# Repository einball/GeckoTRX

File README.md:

# GeckoTRX
GeckoTRX Assembly Design Files

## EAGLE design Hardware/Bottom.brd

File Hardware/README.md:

# GeckoTRX Hardware Design Files

GeckoTRX Hardware Repository

## Getting Started

GeckoTRX is a palm-sized Software Defined Radio with a focus on my own education and be a fun project in my spare time. The repository you are looking at is hosting the front assembly of the project, both hardware design files and software source files required to build the project. If you haven't done any programming or software development yet, or just want to download the latest release of the firmware, you may want to have a look at the [Quickstart Guide](#).

## Prerequisites

In order to view the hardware design files, you will need to obtain a copy of [Autodesk's EagleCAD](https://www.autodesk.com/products/eagle/) which is freely available to view the hardware design files. 

The front assembly uses a EFM8BB1 microcontroller which features a 8051 core alongside with the neccessary peripherals to drive the LED's to indicate the transceivers status.

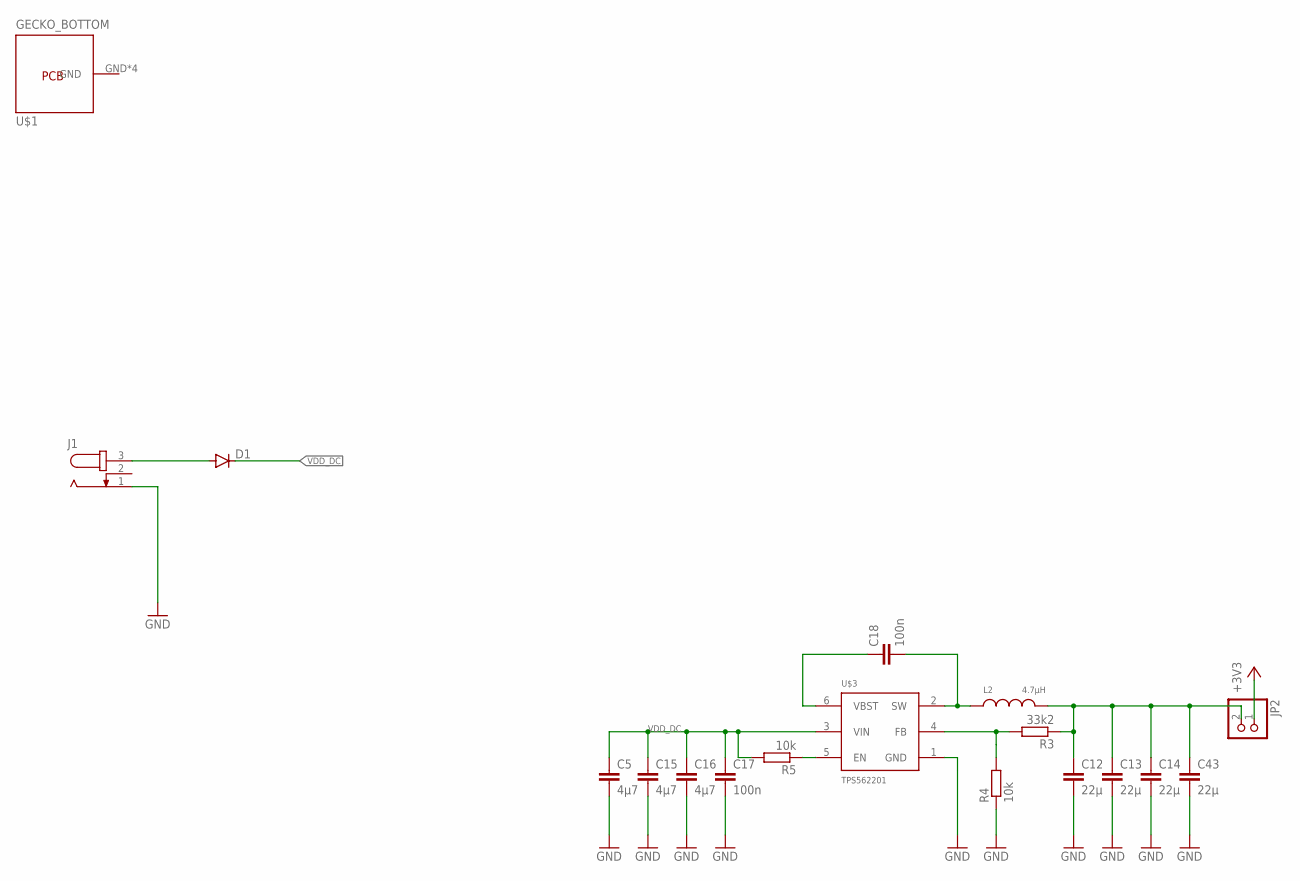
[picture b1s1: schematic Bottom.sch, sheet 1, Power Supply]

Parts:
C5, C15, C16: 4µ7; C0805
C12, C13, C14, C43: 22µ; C0805
C17, C18: 100n; C0805
D1: DIODE-SMB; SMB
J1: JACK-PLUG0; SPC4077
JP2: PINHD-1X2; 1X02
L2: 4.7µH; WE-MAPI_3015/3020
R3: 33k2; R0805
R4, R5: 10k; R0805
U$1: GECKO_BOTTOM
U$3: TPS562201; SOT95P280X110-6

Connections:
+3V3: JP2.1; also elsewhere on the board
GND: C5.2, C12.2, C13.2, C14.2, C15.2, C16.2, C17.2, C43.2, J1.1, R4.1, U$3.1 (GND); also elsewhere on the board
unnamed: D1.A, J1.3
unnamed: C18.1, U$3.6 (VBST)
unnamed: C18.2, L2.1, U$3.2 (SW)
unnamed: R3.2, R4.2, U$3.4 (FB)
unnamed: C12.1, C13.1, C14.1, C43.1, JP2.2, L2.2, R3.1
VDD_DC: C5.1, C15.1, C16.1, C17.1, D1.C, R5.2, U$3.3 (VIN)
VREG_VDD3V3_EN: R5.1, U$3.5 (EN)

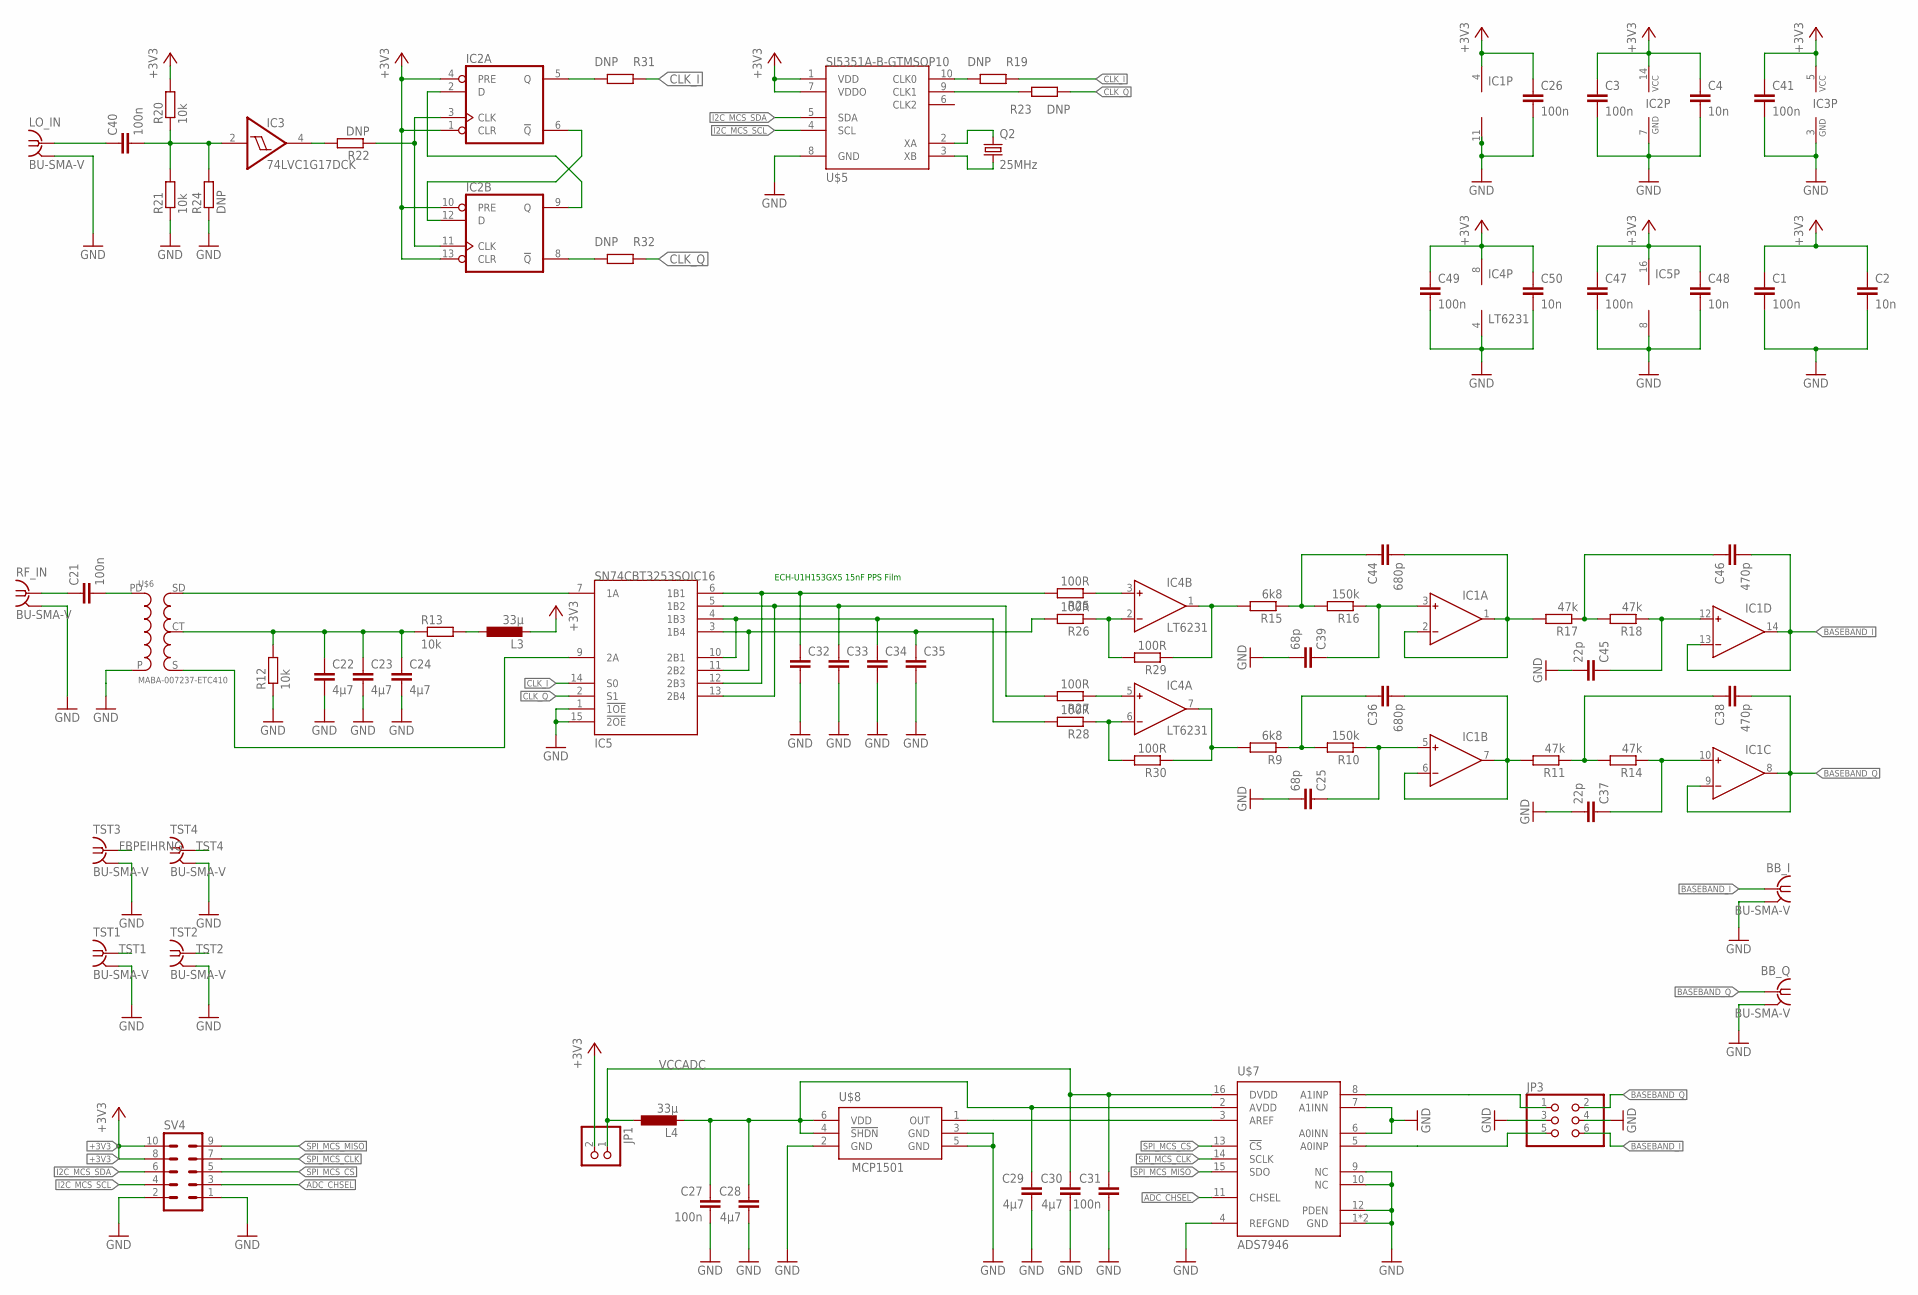
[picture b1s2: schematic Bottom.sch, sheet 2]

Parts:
BB_I: BU-SMA-V
BB_Q: BU-SMA-V
C1, C3, C21, C26, C27, C31, C40, C41, C47, C49: 100n; C0603
C2, C4, C48, C50: 10n; C0603
C22, C23, C24, C28, C29, C30: 4µ7; C0805
C25, C39: 68p; C0603
C32, C33, C34, C35: C-EUC1206; C1206
C36, C44: 680p; C0603
C37, C45: 22p; C0603
C38, C46: 470p; C0603
IC1: OP491SOIC_N14; SOIC127P600X155-14
IC2: 74AC74D; SO14
IC3: 74LVC1G17DCK; SC70-5
IC4: LT6231; SO8
IC5: SN74CBT3253SOIC16; SOIC127P600X175-16
JP1: PINHD-1X2; 1X02
JP3: PINHD-2X3; 2X03
L3, L4: 33µ; L2012C
LO_IN: BU-SMA-V
Q2: 25MHz; ABM10W
R9, R15: 6k8; R0603
R10, R16: 150k; R0603
R11, R14, R17, R18: 47k; R0603
R12, R13, R20, R21: 10k; R0603
R19, R22, R23, R24, R31, R32: DNP; R0603
R25, R26, R27, R28, R29, R30: 100R; R0603
RF_IN: BU-SMA-V
SV4: MA05-2
TST1, TST2, TST3, TST4: BU-SMA-V
U$5: SI5351A-B-GTMSOP10; SOP50P490X110-10
U$6: MABA-007237-ETC410
U$7: ADS7946; QFN50P300X300X80-17T170
U$8: MCP1501; SOT95P280X110-6

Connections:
+3V3: C1.1, C2.1, C3.1, C4.1, C26.1, C41.1, C47.1, C48.1, C49.1, C50.1, IC1.4 (V+), IC2.1 (CLR), IC2.4 (PRE), IC2.10 (PRE), IC2.13 (CLR), IC2.14 (VCC), IC3.5 (VCC), IC4.8 (V+), IC5.16 (V+), JP1.2, L3.2, R20.2, SV4.8, SV4.10, U$5.1 (VDD), U$5.7 (VDDO); also elsewhere on the board
ADC_CHSEL: SV4.3, U$7.11 (CHSEL)
BASEBAND_I: BB_I.1, C46.2, IC1.13 (IN-), IC1.14 (OUT), JP3.6
BASEBAND_Q: BB_Q.1, C38.2, IC1.8 (OUT), IC1.9 (IN-), JP3.2
CLK_I: IC5.14 (S0), R19.1, R31.1
CLK_Q: IC5.2 (S1), R23.1, R32.1
FBPEIHRNG: TST3.1
GND: BB_I.2, BB_I.3 (2), BB_I.4 (2), BB_I.5 (2), BB_Q.2, BB_Q.3 (2), BB_Q.4 (2), BB_Q.5 (2), C1.2, C2.2, C3.2, C4.2, C22.2, C23.2, C24.2, C25.2, C26.2, C27.2, C28.2, C29.2, C30.2, C31.2, C32.2, C33.2, C34.2, C35.2, C37.2, C39.2, C41.2, C45.2, C47.2, C48.2, C49.2, C50.2, IC1.11 (V-), IC2.7 (GND), IC3.3 (GND), IC4.4 (V-), IC5.1 (!1OE), IC5.8 (V-), IC5.15 (!2OE), JP3.3, JP3.4, LO_IN.2, LO_IN.3 (2), LO_IN.4 (2), LO_IN.5 (2), R12.1, R21.1, R24.1, RF_IN.2, RF_IN.3 (2), RF_IN.4 (2), RF_IN.5 (2), SV4.1, SV4.2, TST1.2, TST1.3 (2), TST1.4 (2), TST1.5 (2), TST2.2, TST2.3 (2), TST2.4 (2), TST2.5 (2), TST3.2, TST3.3 (2), TST3.4 (2), TST3.5 (2), TST4.2, TST4.3 (2), TST4.4 (2), TST4.5 (2), U$5.8 (GND), U$6.P, U$7.1 (GND), U$7.4 (REFGND), U$7.6 (A0INN), U$7.7 (A1INN), U$7.9 (NC), U$7.10 (NC), U$7.12 (PDEN), U$7.17 (GND), U$8.2 (GND), U$8.3 (GND), U$8.5 (GND); also elsewhere on the board
I2C_MCS_SCL: SV4.4, U$5.4 (SCL)
I2C_MCS_SDA: SV4.6, U$5.5 (SDA)
unnamed: R19.2, U$5.10 (CLK0)
unnamed: IC2.3 (CLK), IC2.11 (CLK), R22.1
unnamed: IC2.6 (!Q), IC2.12 (D)
unnamed: IC2.2 (D), IC2.9 (Q)
unnamed: R23.2, U$5.9 (CLK1)
unnamed: IC4.7 (OUT), R9.2, R30.1
unnamed: C36.1, R9.1, R10.2
unnamed: C25.1, IC1.5 (IN+), R10.1
unnamed: C36.2, IC1.6 (IN-), IC1.7 (OUT), R11.2
unnamed: C21.1, RF_IN.1
unnamed: C21.2, U$6.PD
unnamed: C22.1, C23.1, C24.1, R12.2, R13.1, U$6.CT
unnamed: L3.1, R13.2
unnamed: IC4.3 (IN+), R25.1
unnamed: C32.1, IC5.6 (1B1), IC5.12 (2B3), R25.2
unnamed: JP3.1, U$7.8 (A1INP)
unnamed: U$7.3 (AREF), U$8.1 (OUT)
unnamed: C27.1, C28.1, C29.1, L4.2, U$7.2 (AVDD), U$8.4 (!SHDN), U$8.6 (VDD)
unnamed: JP3.5, U$7.5 (A0INP)
unnamed: C38.1, R11.1, R14.2
unnamed: C34.1, IC5.4 (1B3), IC5.10 (2B1), R28.2
unnamed: C37.1, IC1.10 (IN+), R14.1
unnamed: IC4.2 (IN-), R26.1, R29.2
unnamed: Q2.1, U$5.3 (XB)
unnamed: C44.1, R15.1, R16.2
unnamed: C39.1, IC1.3 (IN+), R16.1
unnamed: C44.2, IC1.1 (OUT), IC1.2 (IN-), R17.2
unnamed: IC4.5 (IN+), R27.1
unnamed: C40.1, LO_IN.1
unnamed: C40.2, IC3.2 (I), R20.1, R21.2, R24.2
unnamed: IC3.4 (O), R22.2
unnamed: C46.1, R17.1, R18.2
unnamed: IC5.9 (2A), U$6.S
unnamed: IC5.7 (1A), U$6.SD
unnamed: C45.1, IC1.12 (IN+), R18.1
unnamed: IC4.6 (IN-), R28.1, R30.2
unnamed: Q2.3 (2), U$5.2 (XA)
unnamed: IC4.1 (OUT), R15.2, R29.1
unnamed: IC2.8 (!Q), R32.2
unnamed: IC2.5 (Q), R31.2
unnamed: C35.1, IC5.3 (1B4), IC5.11 (2B2), R26.2
unnamed: C33.1, IC5.5 (1B2), IC5.13 (2B4), R27.2
SPI_MCS_CLK: SV4.7, U$7.14 (SCLK)
SPI_MCS_CS: SV4.5, U$7.13 (!CS)
SPI_MCS_MISO: SV4.9, U$7.15 (SDO)
TST1: TST1.1
TST2: TST2.1
TST4: TST4.1
VCCADC: C30.1, C31.1, JP1.1, L4.1, U$7.16 (DVDD)

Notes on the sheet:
ECH-U1H153GX5 15nF PPS Film

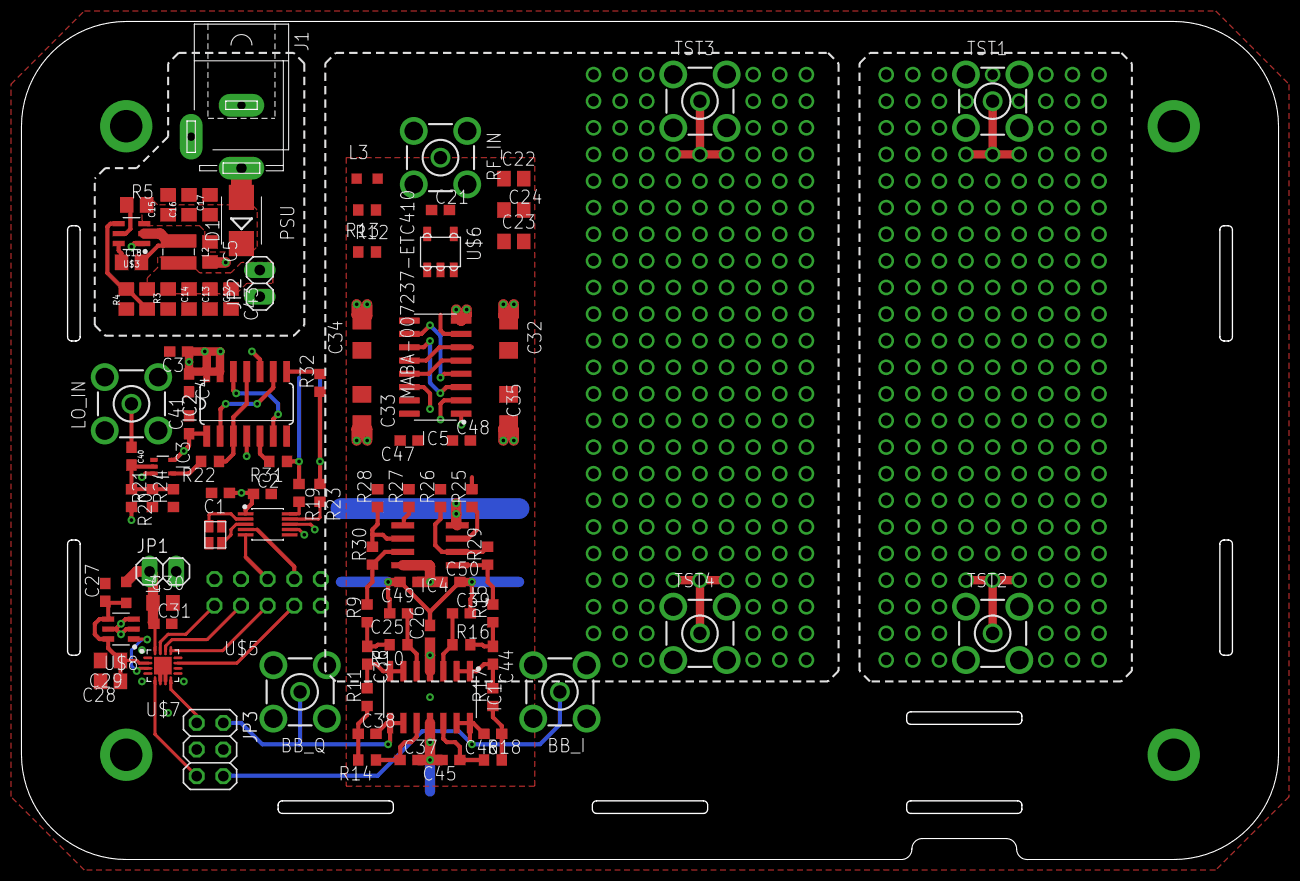
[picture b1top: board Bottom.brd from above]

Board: 4 copper layers, 120.0 x 80.0 mm, 97 parts (1 on the bottom side), 62 nets.

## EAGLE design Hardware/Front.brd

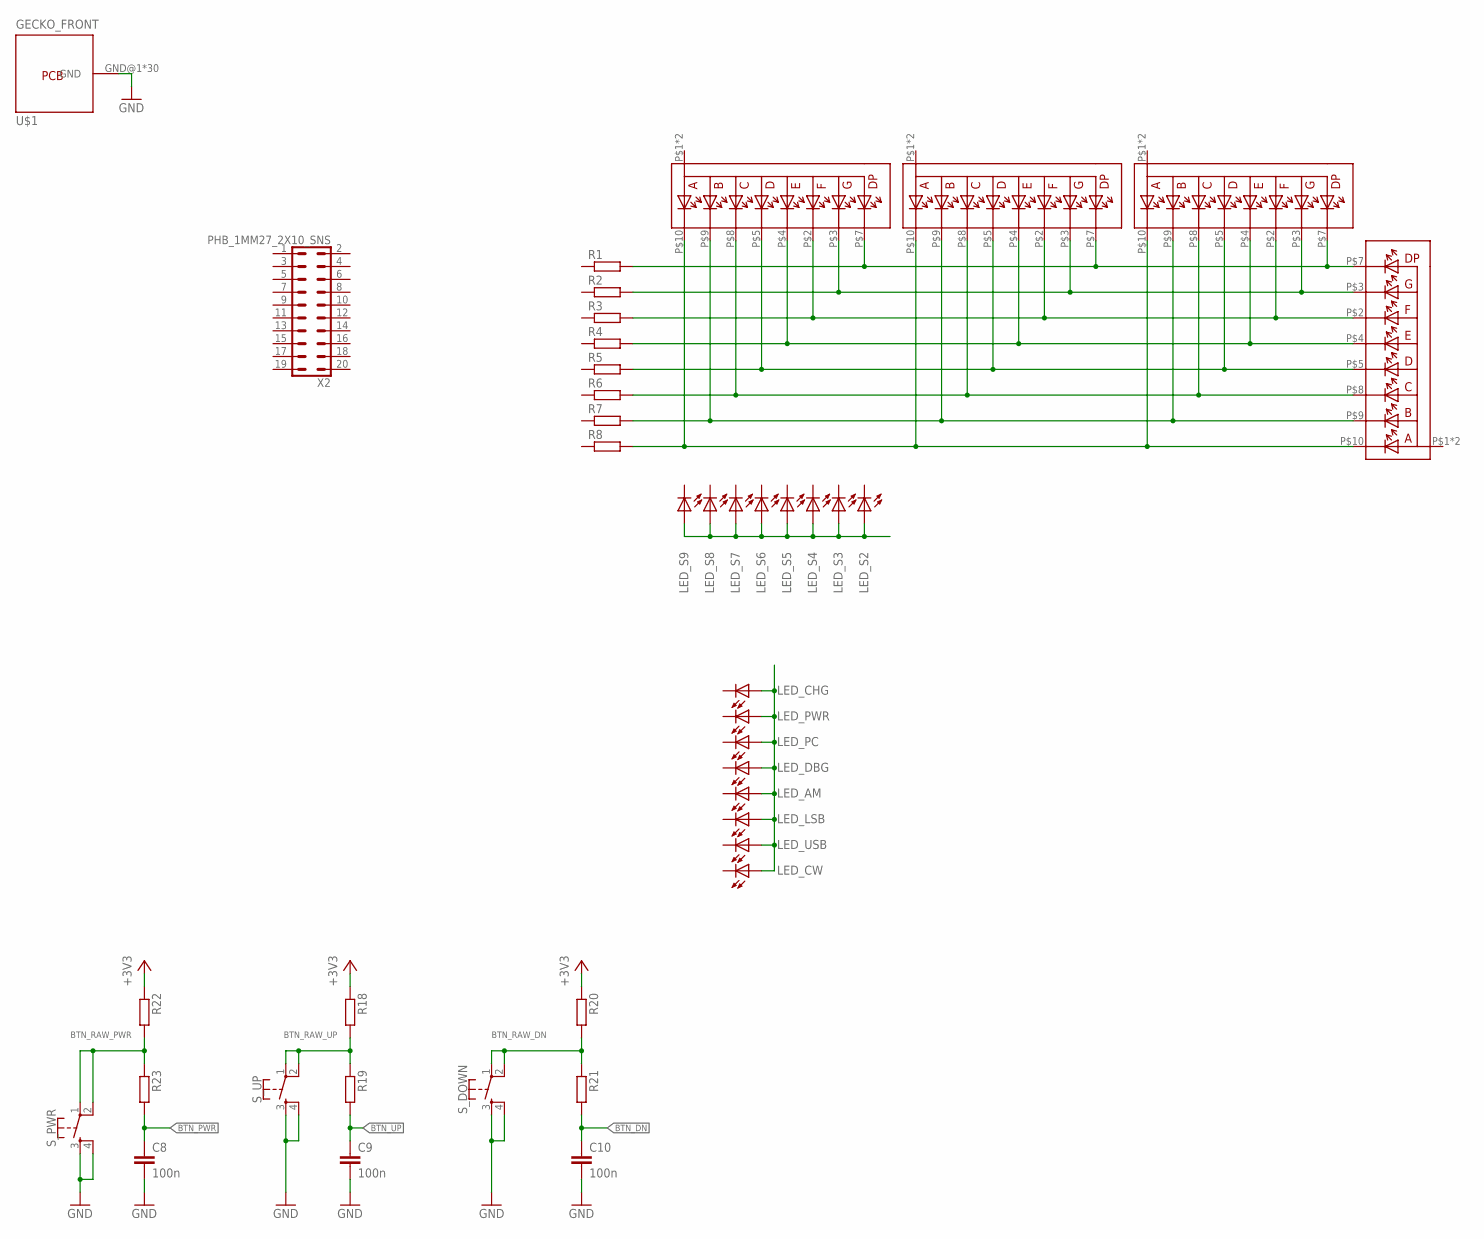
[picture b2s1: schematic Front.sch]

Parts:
C8, C9, C10: 100n; C0402
D3: HDSP-C3E1; 7SEG_THT
LED_AM: LEDCHIPLED_0603; CHIPLED_0603; MPN SML-E12UWT86
LED_CHG: LEDCHIPLED_0603; CHIPLED_0603; MPN SML-E12UWT86
LED_CW: LEDCHIPLED_0603; CHIPLED_0603; MPN SML-E12UWT86
LED_DBG: LEDCHIPLED_0603; CHIPLED_0603; MPN SML-E12UWT86
LED_LSB: LEDCHIPLED_0603; CHIPLED_0603; MPN SML-E12UWT86
LED_PC: LEDCHIPLED_0603; CHIPLED_0603; MPN SML-E12UWT86
LED_PWR: LEDCHIPLED_0603; CHIPLED_0603; MPN SML-E12UWT86
LED_S2, LED_S3, LED_S4, LED_S5, LED_S6, LED_S7, LED_S8, LED_S9: LEDCHIPLED_0603; CHIPLED_0603; MPN SML-E12UWT86
LED_USB: LEDCHIPLED_0603; CHIPLED_0603; MPN SML-E12UWT86
R1, R2, R3, R4, R5, R6, R7, R8, R18, R19, R20, R21, R22, R23: R-EU_R0402; R0402
S_DOWN: MOMENTARY-SWITCH-SPST-2-SMD-4.6X2.8MM; TACTILE_SWITCH_SMD_4.6X2.8MM
S_PWR: MOMENTARY-SWITCH-SPST-2-SMD-4.6X2.8MM; TACTILE_SWITCH_SMD_4.6X2.8MM
S_UP: MOMENTARY-SWITCH-SPST-2-SMD-4.6X2.8MM; TACTILE_SWITCH_SMD_4.6X2.8MM
U$1: GECKO_FRONT
U$9, U$10, U$11: HDSP-C3E1; 7SEG_THT
X2: PHB_1MM27_2X10_SNS

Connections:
+3V3: R18.1, R20.1, R22.1
BTN_DN: C10.1, R21.2
BTN_PWR: C8.1, R23.2
BTN_RAW_DN: R20.2, R21.1, S_DOWN.1, S_DOWN.2
BTN_RAW_PWR: R22.2, R23.1, S_PWR.1, S_PWR.2
BTN_RAW_UP: R18.2, R19.1, S_UP.1, S_UP.2
BTN_UP: C9.1, R19.2
GND: C8.2, C9.2, C10.2, S_DOWN.3, S_DOWN.4, S_PWR.3, S_PWR.4, S_UP.3, S_UP.4, U$1.GND@1, U$1.GND@2, U$1.GND@3, U$1.GND@4, U$1.GND@5, U$1.GND@6, U$1.GND@7, U$1.GND@8, U$1.GND@9, U$1.GND@10, U$1.GND@11, U$1.GND@12, U$1.GND@13, U$1.GND@14, U$1.GND@15, U$1.GND@16, U$1.GND@17, U$1.GND@18, U$1.GND@19, U$1.GND@20, U$1.GND@21, U$1.GND@22, U$1.GND@23, U$1.GND@24, U$1.GND@25, U$1.GND@26, U$1.GND@27, U$1.GND@28, U$1.GND@29, U$1.GND@30
unnamed: D3.P$7 (DP), R1.2, U$9.P$7 (DP), U$10.P$7 (DP), U$11.P$7 (DP)
unnamed: D3.P$3 (G), R2.2, U$9.P$3 (G), U$10.P$3 (G), U$11.P$3 (G)
unnamed: D3.P$2 (F), R3.2, U$9.P$2 (F), U$10.P$2 (F), U$11.P$2 (F)
unnamed: D3.P$4 (E), R4.2, U$9.P$4 (E), U$10.P$4 (E), U$11.P$4 (E)
unnamed: D3.P$5 (D), R5.2, U$9.P$5 (D), U$10.P$5 (D), U$11.P$5 (D)
unnamed: D3.P$8 (C), R6.2, U$9.P$8 (C), U$10.P$8 (C), U$11.P$8 (C)
unnamed: D3.P$9 (B), R7.2, U$9.P$9 (B), U$10.P$9 (B), U$11.P$9 (B)
unnamed: D3.P$10 (A), R8.2, U$9.P$10 (A), U$10.P$10 (A), U$11.P$10 (A)
unnamed: LED_AM.A, LED_CHG.A, LED_CW.A, LED_DBG.A, LED_LSB.A, LED_PC.A, LED_PWR.A, LED_USB.A
unnamed: LED_S2.A, LED_S3.A, LED_S4.A, LED_S5.A, LED_S6.A, LED_S7.A, LED_S8.A, LED_S9.A

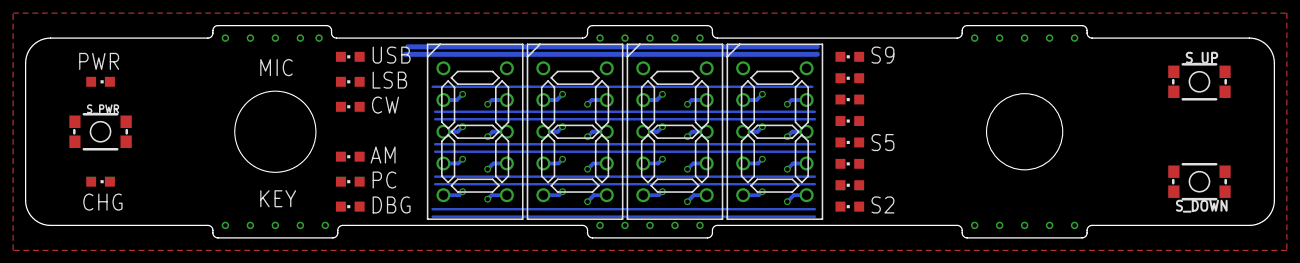
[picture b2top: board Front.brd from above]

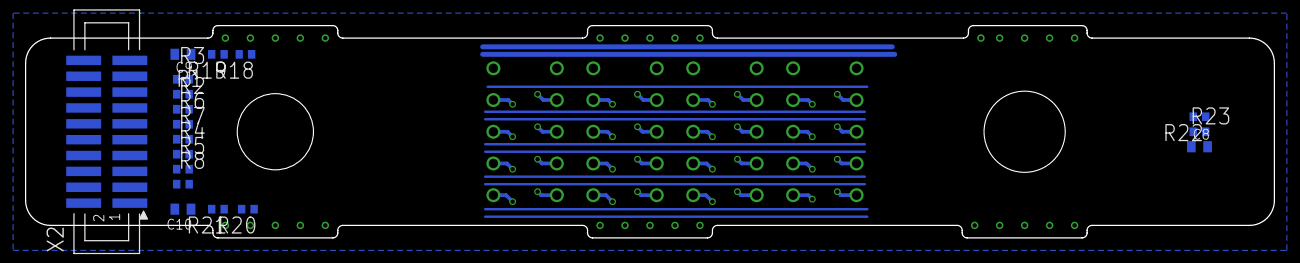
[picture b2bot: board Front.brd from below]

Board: 2 copper layers, 100.0 x 17.0 mm, 42 parts (18 on the bottom side), 18 nets.

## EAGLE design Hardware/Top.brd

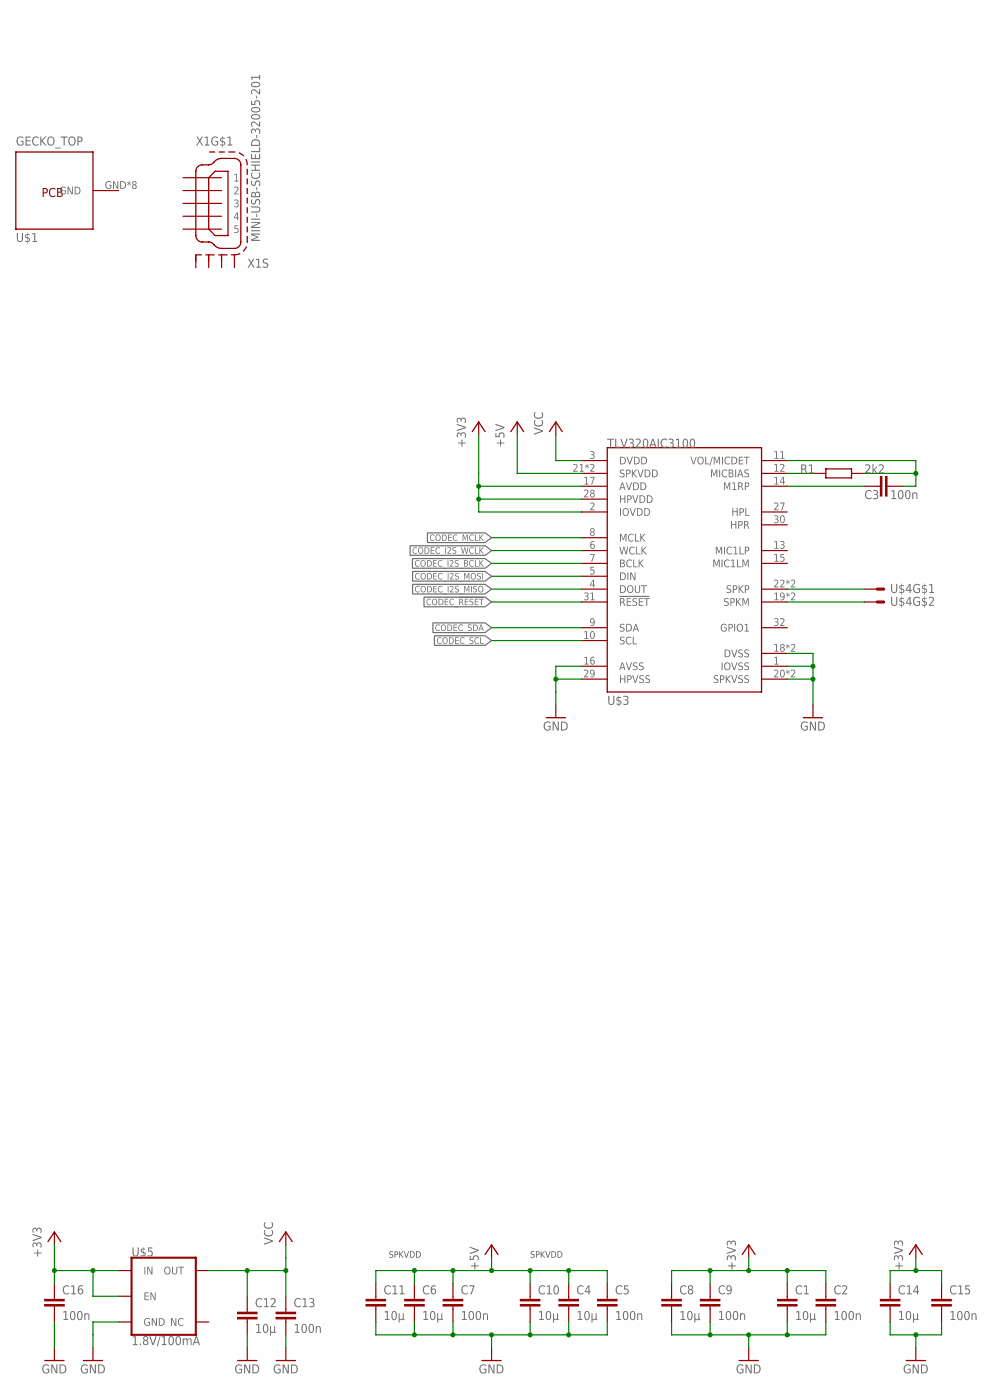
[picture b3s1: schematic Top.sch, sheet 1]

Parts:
C1, C4, C6, C8, C10, C11, C12, C14: 10µ; C0805
C2, C3, C5, C7, C9, C13, C15, C16: 100n; C0805
R1: 2k2; R0402
U$1: GECKO_TOP
U$3: TLV320AIC3100; QFN32
U$4: JST-SH-2-SMT
U$5: 1.8V/100mA; SC70
X1: MINI-USB-SCHIELD-32005-201; 32005-201

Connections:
+3V3: C1.1, C2.1, C8.1, C9.1, C14.1, C15.1, C16.1, U$3.2 (IOVDD), U$3.17 (AVDD), U$3.28 (HPVDD), U$5.1 (IN), U$5.3 (EN)
+5V: C4.1, C5.1, C6.1, C7.1, C10.1, C11.1, U$3.21 (SPKVDD), U$3.24 (SPKVDD)
CODEC_!RESET: U$3.31 (!RESET)
CODEC_I2S_BCLK: U$3.7 (BCLK); also elsewhere on the board
CODEC_I2S_MISO: U$3.4 (DOUT); also elsewhere on the board
CODEC_I2S_MOSI: U$3.5 (DIN); also elsewhere on the board
CODEC_I2S_WCLK: U$3.6 (WCLK); also elsewhere on the board
CODEC_MCLK: U$3.8 (MCLK); also elsewhere on the board
CODEC_SCL: U$3.10 (SCL)
CODEC_SDA: U$3.9 (SDA)
GND: C1.2, C2.2, C4.2, C5.2, C6.2, C7.2, C8.2, C9.2, C10.2, C11.2, C12.2, C13.2, C14.2, C15.2, C16.2, U$3.1 (IOVSS), U$3.16 (AVSS), U$3.18 (DVSS), U$3.20 (SPKVSS), U$3.25 (SPKVSS), U$3.29 (HPVSS), U$3.EXP (DVSS), U$5.2 (GND); also elsewhere on the board
unnamed: U$3.22 (SPKP), U$3.26 (SPKP), U$4.1
unnamed: R1.1, U$3.12 (MICBIAS)
unnamed: C3.1, U$3.14 (M1RP)
unnamed: C3.2, R1.2, U$3.11 (VOL/MICDET)
unnamed: U$3.19 (SPKM), U$3.23 (SPKM), U$4.2
VCC: C12.1, C13.1, U$3.3 (DVDD), U$5.5 (OUT); also elsewhere on the board

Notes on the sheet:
SPKVDD

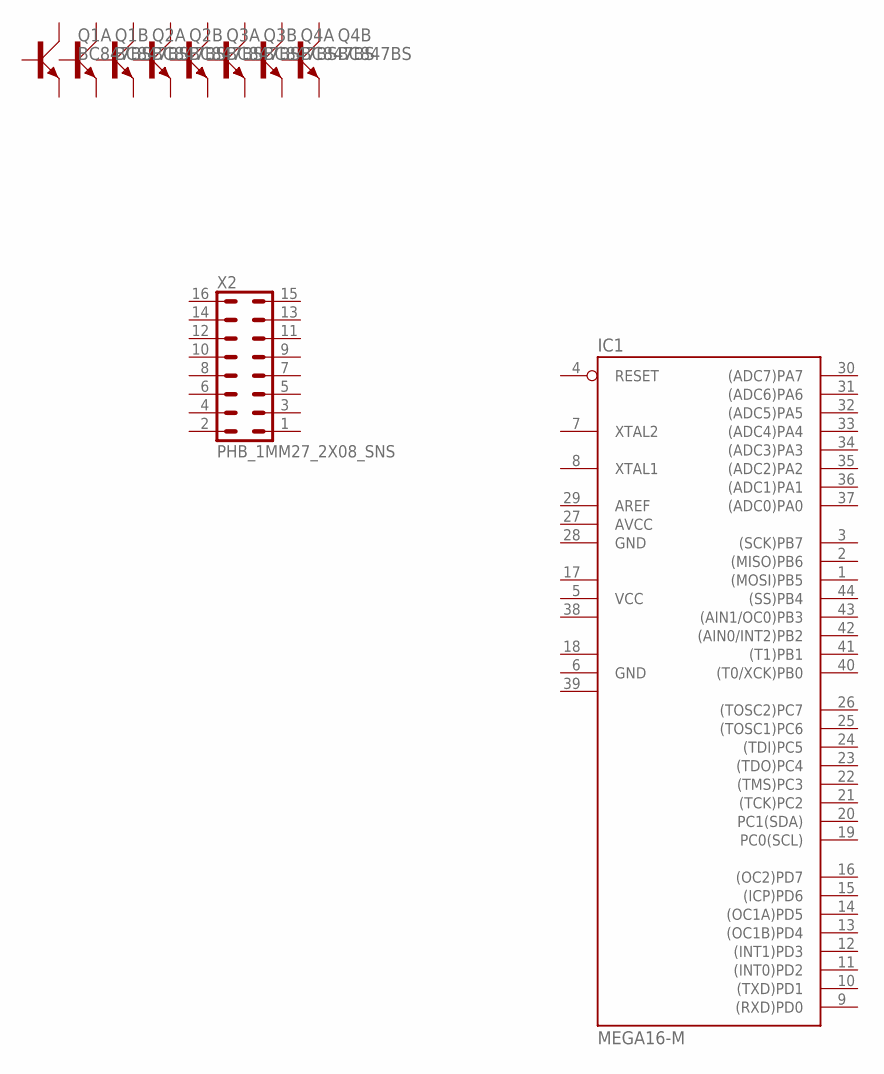
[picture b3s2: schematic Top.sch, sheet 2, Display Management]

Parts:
IC1: MEGA16-M; MLF44
Q1, Q2, Q3, Q4: BC847BS; SOT363_PHILIPS
X2: PHB_1MM27_2X08_SNS

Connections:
AVCC: IC1.27 (AVCC)
GND: IC1.6 (GND), IC1.28 (GND); also elsewhere on the board
GND1: IC1.18 (GND1)
GND2: IC1.39 (GND2)
VCC: IC1.5 (VCC); also elsewhere on the board
VCC1: IC1.17 (VCC1)
VCC2: IC1.38 (VCC2)

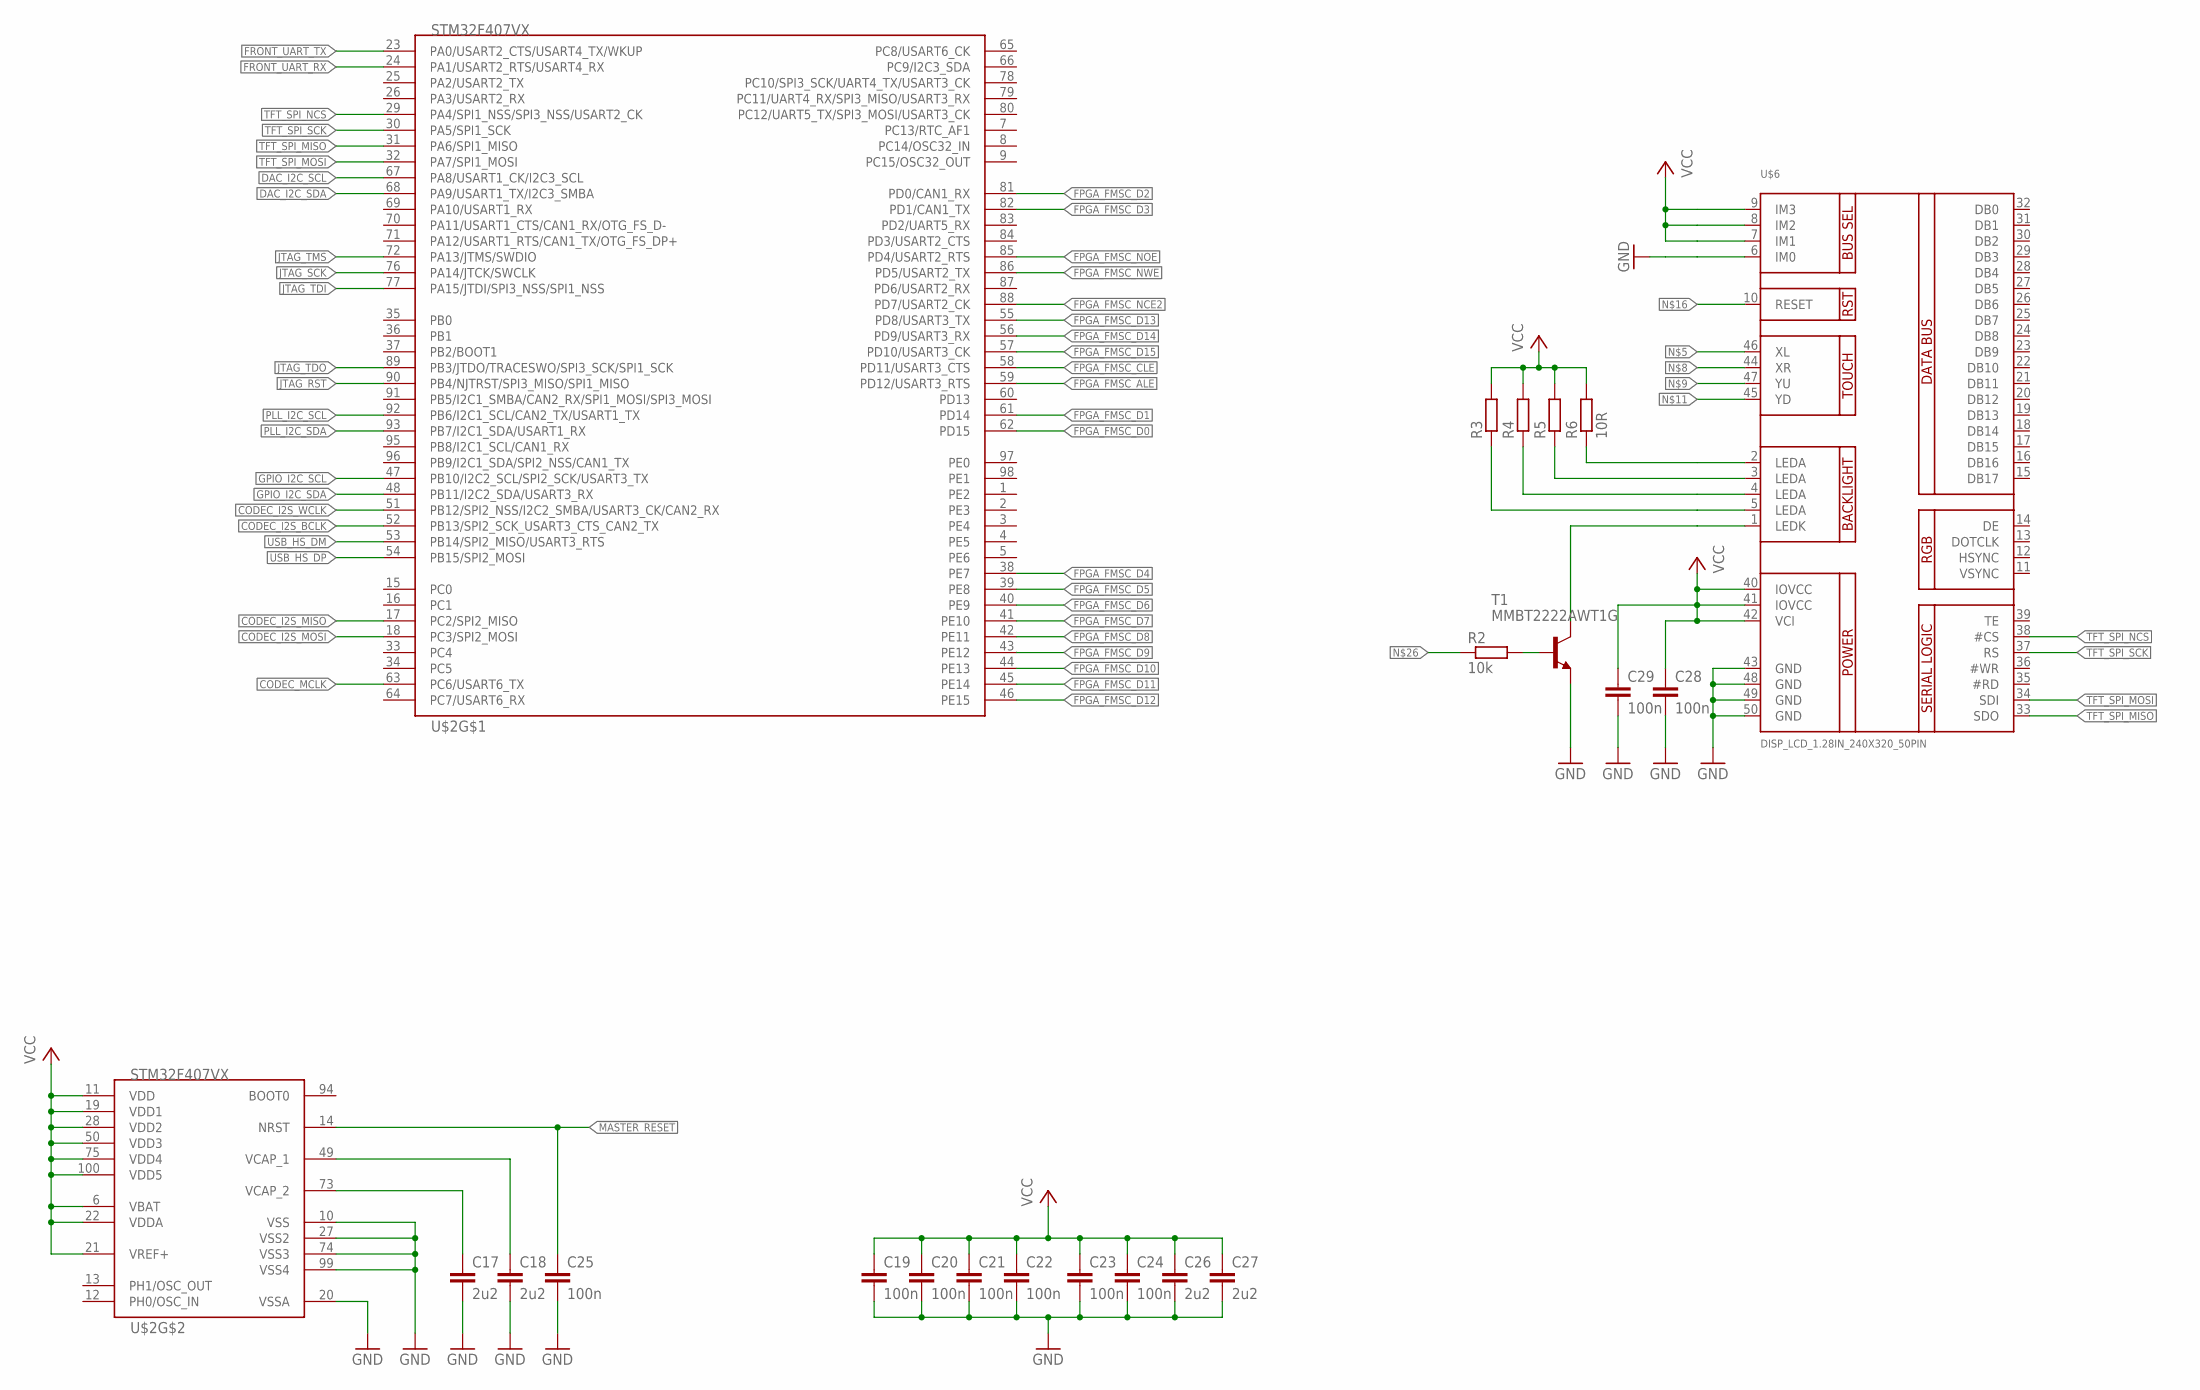
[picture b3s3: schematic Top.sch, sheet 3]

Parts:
C17, C18, C26, C27: 2u2; C0805
C19, C20, C21, C22, C23, C24, C25, C28, C29: 100n; C0402
R2: 10k; R0402
R3, R4, R5, R6: 10R; R0805
T1: MMBT2222AWT1G; SOT23-BEC
U$2: STM32F407VX; LQFP100
U$6: DISP_LCD_1.28IN_240X320_50PIN; TFT_2.83IN_240X320_50PIN

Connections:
!MASTER_RESET: C25.1, U$2.14 (NRST)
CODEC_I2S_BCLK: U$2.52 (PB13/SPI2_SCK_USART3_CTS_CAN2_TX); also elsewhere on the board
CODEC_I2S_MISO: U$2.17 (PC2/SPI2_MISO); also elsewhere on the board
CODEC_I2S_MOSI: U$2.18 (PC3/SPI2_MOSI); also elsewhere on the board
CODEC_I2S_WCLK: U$2.51 (PB12/SPI2_NSS/I2C2_SMBA/USART3_CK/CAN2_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); also elsewhere on the board
CODEC_MCLK: U$2.63 (PC6/USART6_TX); also elsewhere on the board
DAC_I2C_SCL: U$2.67 (PA8/USART1_CK/I2C3_SCL)
DAC_I2C_SDA: U$2.68 (PA9/USART1_TX/I2C3_SMBA)
FPGA_FMSC_ALE: U$2.59 (PD12/USART3_RTS)
FPGA_FMSC_CLE: U$2.58 (PD11/USART3_CTS)
FPGA_FMSC_D0: U$2.62 (PD15)
FPGA_FMSC_D1: U$2.61 (PD14)
FPGA_FMSC_D2: U$2.81 (PD0/CAN1_RX)
FPGA_FMSC_D3: U$2.82 (PD1/CAN1_TX)
FPGA_FMSC_D4: U$2.38 (PE7)
FPGA_FMSC_D5: U$2.39 (PE8)
FPGA_FMSC_D6: U$2.40 (PE9)
FPGA_FMSC_D7: U$2.41 (PE10)
FPGA_FMSC_D8: U$2.42 (PE11)
FPGA_FMSC_D9: U$2.43 (PE12)
FPGA_FMSC_D10: U$2.44 (PE13)
FPGA_FMSC_D11: U$2.45 (PE14)
FPGA_FMSC_D12: U$2.46 (PE15)
FPGA_FMSC_D13: U$2.55 (PD8/USART3_TX)
FPGA_FMSC_D14: U$2.56 (PD9/USART3_RX)
FPGA_FMSC_D15: U$2.57 (PD10/USART3_CK)
FPGA_FMSC_NCE2: U$2.88 (PD7/USART2_CK)
FPGA_FMSC_NOE: U$2.85 (PD4/USART2_RTS)
FPGA_FMSC_NWE: U$2.86 (PD5/USART2_TX)
FRONT_UART_RX: U$2.24 (PA1/USART2_RTS/USART4_RX)
FRONT_UART_TX: U$2.23 (PA0/USART2_CTS/USART4_TX/WKUP)
GND: C17.2, C18.2, C19.2, C20.2, C21.2, C22.2, C23.2, C24.2, C25.2, C26.2, C27.2, C28.2, C29.2, T1.E, U$2.10 (VSS), U$2.20 (VSSA), U$2.27 (VSS2), U$2.74 (VSS3), U$2.99 (VSS4), U$6.6 (IM0), U$6.43 (GND), U$6.48 (GND), U$6.49 (GND), U$6.50 (GND); also elsewhere on the board
GPIO_I2C_SCL: U$2.47 (PB10/I2C2_SCL/SPI2_SCK/USART3_TX)
GPIO_I2C_SDA: U$2.48 (PB11/I2C2_SDA/USART3_RX)
JTAG_RST: U$2.90 (PB4/NJTRST/SPI3_MISO/SPI1_MISO)
JTAG_SCK: U$2.76 (PA14/JTCK/SWCLK)
JTAG_TDI: U$2.77 (PA15/JTDI/SPI3_NSS/SPI1_NSS)
JTAG_TDO: U$2.89 (PB3/JTDO/TRACESWO/SPI3_SCK/SPI1_SCK)
JTAG_TMS: U$2.72 (PA13/JTMS/SWDIO)
unnamed: C17.1, U$2.73 (VCAP_2)
unnamed: C18.1, U$2.49 (VCAP_1)
unnamed: T1.C, U$6.1 (LEDK)
unnamed: R6.1, U$6.2 (LEDA)
unnamed: R5.1, U$6.3 (LEDA)
unnamed: R4.1, U$6.4 (LEDA)
unnamed: R3.1, U$6.5 (LEDA)
unnamed: R2.2, T1.B
PLL_I2C_SCL: U$2.92 (PB6/I2C1_SCL/CAN2_TX/USART1_TX)
PLL_I2C_SDA: U$2.93 (PB7/I2C1_SDA/USART1_RX)
TFT_SPI_MISO: U$2.31 (PA6/SPI1_MISO), U$6.33 (SDO)
TFT_SPI_MOSI: U$2.32 (PA7/SPI1_MOSI), U$6.34 (SDI)
TFT_SPI_NCS: U$2.29 (PA4/SPI1_NSS/SPI3_NSS/USART2_CK), U$6.38 (#CS)
TFT_SPI_SCK: U$2.30 (PA5/SPI1_SCK), U$6.37 (RS)
USB_HS_DM: U$2.53 (PB14/SPI2_MISO/USART3_RTS)
USB_HS_DP: U$2.54 (PB15/SPI2_MOSI)
VCC: C19.1, C20.1, C21.1, C22.1, C23.1, C24.1, C26.1, C27.1, C28.1, C29.1, R3.2, R4.2, R5.2, R6.2, U$2.6 (VBAT), U$2.11 (VDD), U$2.19 (VDD1), U$2.21 (VREF+), U$2.22 (VDDA), U$2.28 (VDD2), U$2.50 (VDD3), U$2.75 (VDD4), U$2.100 (VDD5), U$6.7 (IM1), U$6.8 (IM2), U$6.40 (IOVCC), U$6.41 (IOVCC), U$6.42 (VCI); also elsewhere on the board

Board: 2 copper layers, 49 parts (1 on the bottom side), 27 nets, no tracks yet.

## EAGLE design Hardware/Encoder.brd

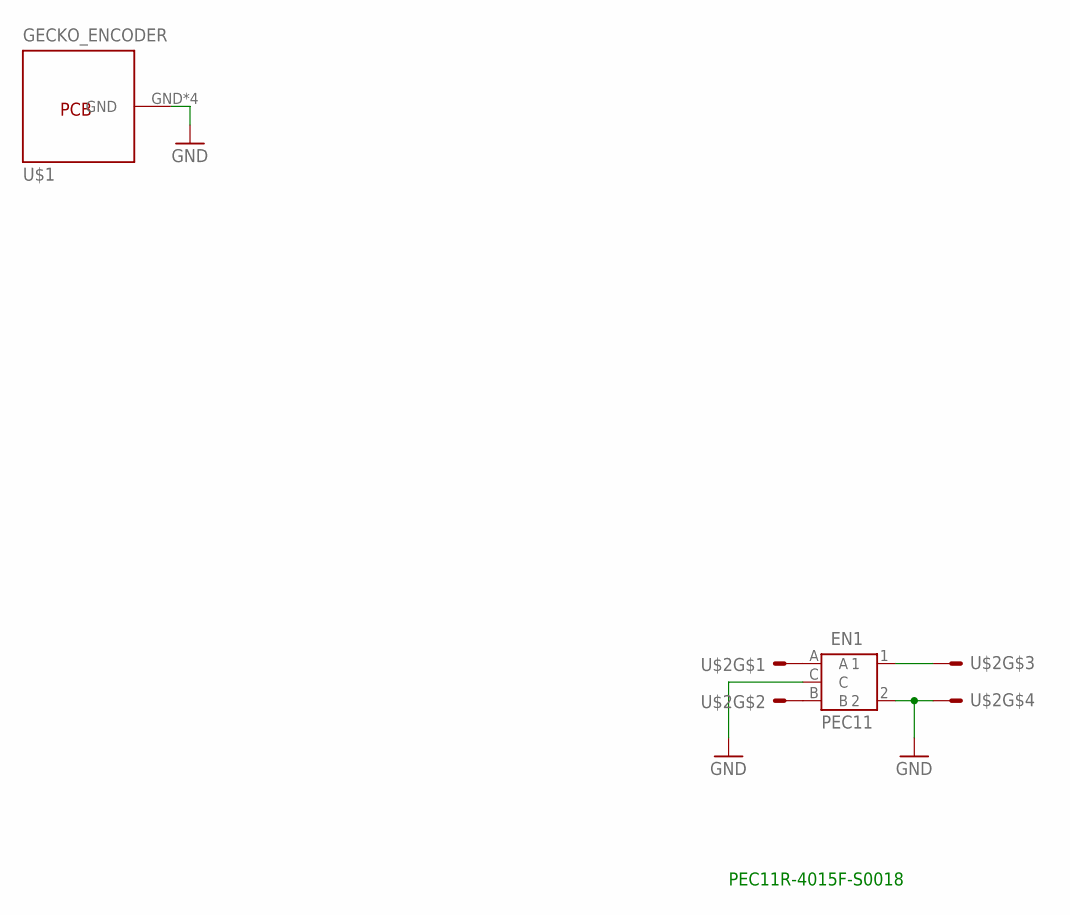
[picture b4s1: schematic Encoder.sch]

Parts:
EN1: PEC11; PEC11_4XXXXK-S
U$1: GECKO_ENCODER
U$2: JST-SH-4-SMT

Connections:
GND: EN1.2, EN1.C, U$1.GND, U$1.GND1, U$1.GND2, U$1.GND3, U$2.P$4
unnamed: EN1.A, U$2.P$1
unnamed: EN1.B, U$2.P$2
unnamed: EN1.1, U$2.P$3

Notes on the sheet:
PEC11R-4015F-S0018

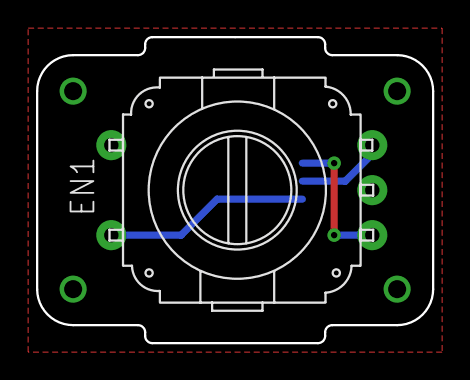
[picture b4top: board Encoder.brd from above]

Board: 2 copper layers, 22.0 x 17.0 mm, 3 parts (1 on the bottom side), 4 nets.

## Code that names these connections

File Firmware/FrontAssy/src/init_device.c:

/*
 * EFM8BB1 InitDevice Routines
 *
 * Copyright (c) 2017 Jan Krueger <jan.krueger@nerdhybride.de>
 *
 * No license yet.
 *
 */


#include "init_device.h"

/***************************************************************
* - Pin 02 (P0.0): SPI_SCK			* - Pin 13 (P1.1): BTN_PWR *
* - Pin 01 (P0.1): SPI0_MISO	 	* - Pin 11 (P1.2): BTN_DN  *
* - Pin 20 (P0.2): SPI0_MOSI	 	* - Pin 10 (P1.3): ENC_A   *
* - Pin 19 (P0.3): SPI0_NSS	 		* - Pin 09 (P1.4): ENC_B   *
* - Pin 18 (P0.4): UART0_TX	 		* - Pin 08 (P1.5): ENC_C   *
* - Pin 17 (P0.5): UART0_RX 	 	* - Pin 07 (P1.6): BTN_UP  *
* - Pin 16 (P0.6): (Unused SDA) 	* - Pin 06 (P2.0): C2D     *
* - Pin 15 (P0.7): (Unused SCL) 	* - Pin 05 (RSTN): C2CK	   *
****************************************************************
* - Pin 04: (VDD): VDD				* - Pin 12 (GND): GND	   *
* - Pin 05: (GND): GND 				* - Pad 01 (PAD): GND	   *
***************************************************************/

void InitDevice(){

	// Clock Select
	CLKSEL 	 = 	CLKDIV__SYSCLK_DIV_8 | CLKSL__HFOSC;			
	
	// Disable Watchdog
	WDTCN = 0xDE;
	WDTCN = 0xDE;

	// XBAR Skipping: Assign UART0, SPI0 signals, skip rest for GPIO
	P0SKIP   = 	B7__NOT_SKIPPED | B6__NOT_SKIPPED | B5__NOT_SKIPPED | B4__NOT_SKIPPED | B3__NOT_SKIPPED | B2__NOT_SKIPPED | B1__NOT_SKIPPED | B0__SKIPPED;

	P1SKIP 	 = 	B7__SKIPPED | B6__SKIPPED | B5__SKIPPED | B4__SKIPPED | B3__SKIPPED | B2__SKIPPED | B1__SKIPPED | B0__SKIPPED;

	// XBAR Priority Assignment
	XBR0  	 =	URT0E__ENABLED | SPI0E__ENABLED;
	XBR1  	 =	0x00;			
	XBR2   	|= 	XBARE__ENABLED | WEAKPUD__PULL_UPS_ENABLED;

	// SPI Config
	SPI0CFG	|= MSTEN__MASTER_ENABLED;
	SPI0CN0 |= SPIEN__ENABLED | NSSMD__4_WIRE_MASTER_NSS_HIGH;

	// UART Config
	SCON0   |= SMODE__8_BIT | REN__RECEIVE_ENABLED;




//	P0MDIN  = ;				// Port 0 Input Mode: Analog / Digital Mode
//	P0MDOUT = ;				// Port 0 Output Mode: Push-Pull / Open-Drain
//	P1MDIN  = ;				// Port 1 Input Mode: Analog / Digital Mode
//	P1MDOUT = ;				// Port 1 Output Mode: Push-Pull / Open-Drain
//	P2MDIN  = ;				// Port 2 Input Mode: Analog / Digital Mode
//	P2MDOUT = ;				// Port 2 Output Mode: Push-Pull / Open-Drain
	
	IE = 0xD0;				// Interrupt Enable:  Enable SPI0, UART0 and global interrupt
	IP = 0x90;				// Interrupt Priority: UART0 High, rest low, IP.7 high as per datasheet

	EIE1 = 0x00;			// Extended Interrupt Enable: Disable all other interrupt sources
	EIP1 = 0x00;

}

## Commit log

2018-10-02 Add gitignore
2018-10-02 Fix Library include in Includes
2018-10-02 Remove multiline expression
2018-10-02 Add cmake support
2018-10-02 Add cmake suport
2018-10-02 Add multiple READMEs
2018-10-17 Add stepdown converters
2018-10-27 Add sides, add Tayloe Detector
2018-11-16 Order sides
2018-11-28 Adds SN74CBT3253 to Bottom
2018-12-11 Finish version 0.1 of front
2018-12-11 Advance layout bottom
2018-12-12 Front board cleanup
2018-12-26 Add RF Buffer
2019-01-10 Add various parts
2019-03-18 Add KiCAD Bottom
2019-03-18 Add KiCAd project file
2019-04-25 Update board Projektarbeit
2019-04-25 KiCAD advancements
2019-07-10 PCB v2 0 airwires
2019-07-12 PCB v2 done
2021-02-04 keine ahnung, aber weitergemacht

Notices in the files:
parts and their libraries:
PowerMagnetics: Copyright: Würth Elektronik
SparkFun-Switches: Licensing: Creative Commons ShareAlike 4.0 International - https://creativecommons.org/licenses/by-sa/4.0
MyLib: Copyright 2012 by Ersan Günes, Quantitec, info@quantitec.de
